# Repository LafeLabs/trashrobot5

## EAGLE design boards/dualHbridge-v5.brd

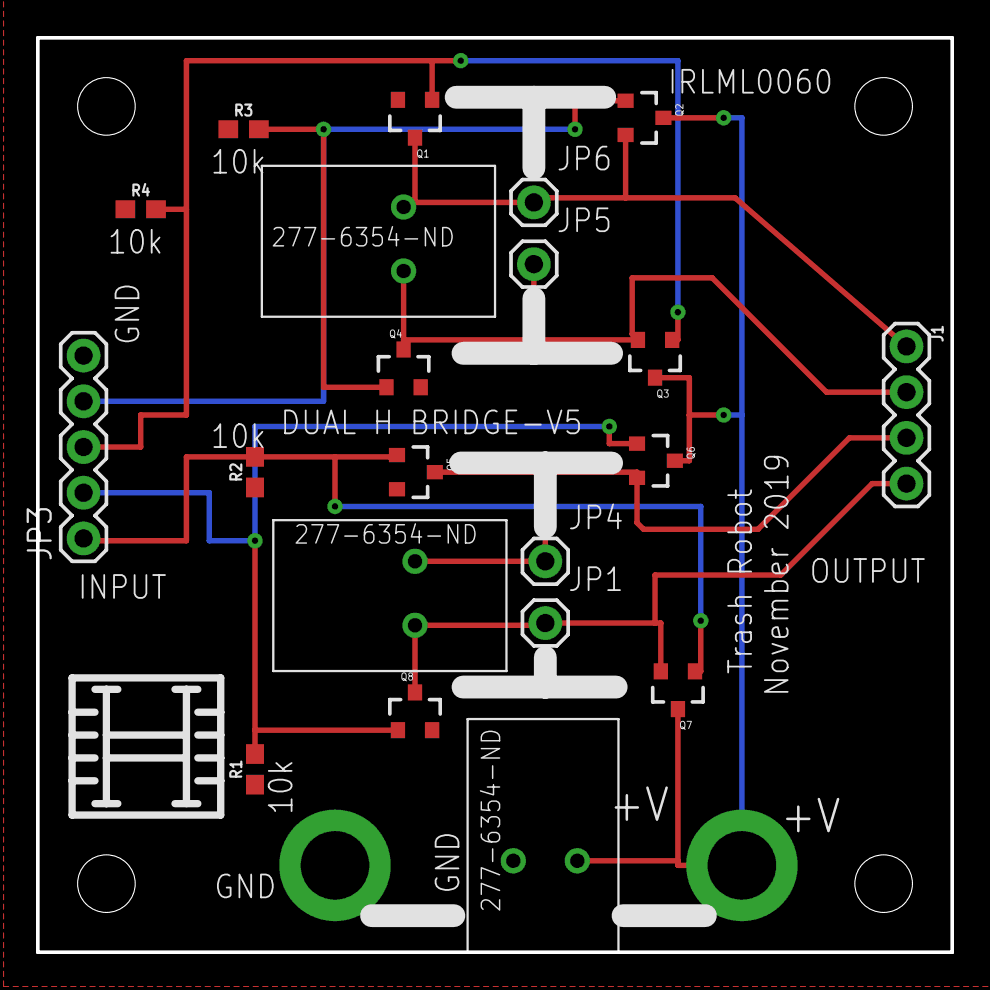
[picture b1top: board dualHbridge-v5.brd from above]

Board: 2 copper layers, 50.8 x 50.8 mm, 23 parts (0 on the bottom side), 10 nets.

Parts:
J1: 1X04
JP1, JP4, JP5, JP6: M01PTH; 1X01@1
JP3: 1X05
JP7, JP8: M01-SMTSO-256-ET; SMTSO-256-ET
Q1, Q2, Q3, Q4, Q5, Q6, Q7, Q8: IRLML0060; SOT-23
R1, R2, R3, R4: 10k; 0603
X1, X2, X3: SPRING-TERMINAL

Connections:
A+: J1.1, JP6.1, Q1.3, Q2.2, X1.P$1
A-: J1.2, JP5.1, Q3.2, Q4.3, X1.P$2
B+: J1.3, JP4.1, Q5.3, Q6.2, X2.P$1
B-: J1.4, JP1.1, Q7.2, Q8.3, X2.P$2
GND: JP3.5, JP8.P$1, Q1.2, Q4.2, Q5.2, Q8.2, R1.1, R2.1, R3.1, R4.1, X3.P$2
unnamed: JP3.4, Q2.1, Q4.1, R3.2
unnamed: JP3.3, Q1.1, Q3.1, R4.2
unnamed: JP3.1, Q5.1, Q7.1, R2.2
unnamed: JP3.2, Q6.1, Q8.1, R1.2
PWR: JP7.P$1, Q2.3, Q3.3, Q6.3, Q7.3, X3.P$1

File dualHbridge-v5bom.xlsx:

REFDES | Value | QTY | Manufacturer | Manufacturer Part Number | Digikey Part Number | package | Price
Q1 | IRLML0060 | 1 | Infineon | IRLML0060 | IRLML0060TRPBFCT-ND |  | 0.25
Q2 | IRLML0060 | 1 | Infineon | IRLML0060 | IRLML0060TRPBFCT-ND |  | 0.25
Q3 | IRLML0060 | 1 | Infineon | IRLML0060 | IRLML0060TRPBFCT-ND |  | 0.25
Q4 | IRLML0060 | 1 | Infineon | IRLML0060 | IRLML0060TRPBFCT-ND |  | 0.25
Q5 | IRLML0060 | 1 | Infineon | IRLML0060 | IRLML0060TRPBFCT-ND |  | 0.25
Q6 | IRLML0060 | 1 | Infineon | IRLML0060 | IRLML0060TRPBFCT-ND |  | 0.25
Q7 | IRLML0060 | 1 | Infineon | IRLML0060 | IRLML0060TRPBFCT-ND |  | 0.25
Q8 | IRLML0060 | 1 | Infineon | IRLML0060 | IRLML0060TRPBFCT-ND |  | 0.25
X1 | spring contact | 3 | Phoenix Contact | 1984963 | 277-6354-ND
X2 |  |  | Phoenix Contact | 1984963 | 277-6354-ND
X3 |  |  | Phoenix Contact | 1984963 | 277-6354-ND
R1 | 10k | 4 | stackpole electronics | ERJ-3EKF3301V | RNCP0603FTD10K0CT-ND | 0603 | 2.7E-2
R2 | 10k |  | stackpole electronics | ERJ-3EKF3301V | RNCP0603FTD10K0CT-ND | 0603 | 2.7E-2
R3 | 10k |  | stackpole electronics | ERJ-3EKF3301V | RNCP0603FTD10K0CT-ND | 0603 | 2.7E-2
R4 | 10k |  | stackpole electronics | ERJ-3EKF3301V | RNCP0603FTD10K0CT-ND | 0603 | 2.7E-2
J1 | 4 pin header | 1 | Samtec | TSW-104-25-G-S-RA |  |  | 0.25
J1 | 5 pin header | 1 | Samtec | TSW-105-25-G-S-RA |  |  | 0.25
total |  |  |  |  |  |  | 2

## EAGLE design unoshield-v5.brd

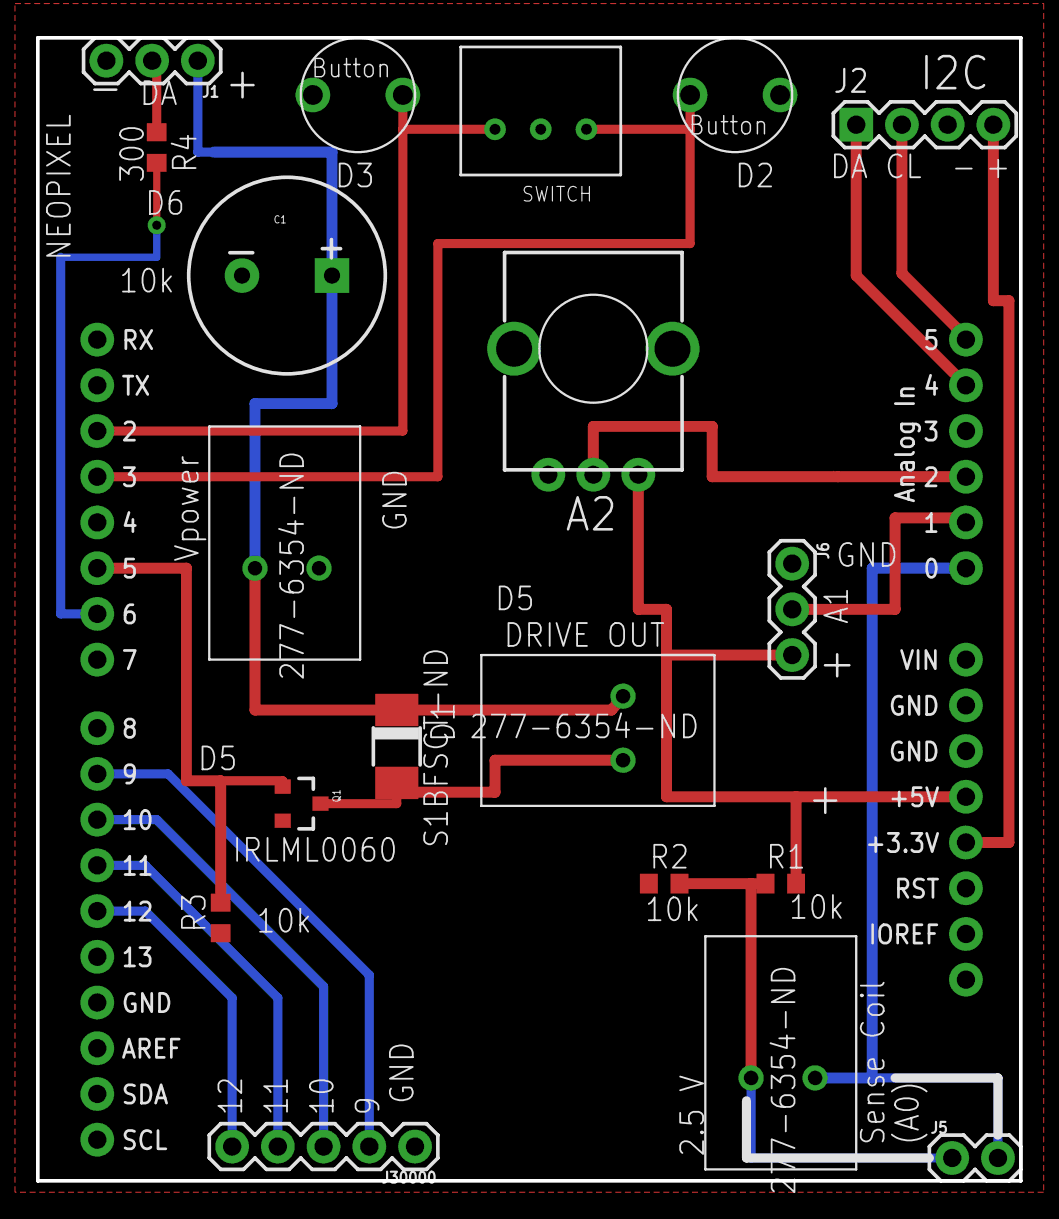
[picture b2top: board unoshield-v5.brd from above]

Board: 2 copper layers, 54.6 x 63.5 mm, 20 parts (0 on the bottom side), 20 nets.

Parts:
C1: 1000uf/25V; CPOL-RADIAL-1000UF-25V-KIT
D1: DO-214AC
J1, J6: 455-1750-1-ND; 1X03
J2: 1X04
J4: ARDUINO_R3_SHIELD; UNO_R3_SHIELD
J5: 1X02
J30000: 1X05
Q1: IRLML0060; SOT-23
R1, R2, R3: 10k; R0603
R4: 330; R0603
R5: 20k; ALPS_POT_KIT
SW1, SW2: BUTTON
SW3: ON-OFF-ON-360-1013-ND; 360-1013-ND
X1, X2, X3: SPRING-TERMINAL

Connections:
5V: J4.5V, J6.3, R1.2, R5.P$3
BUTTON: J4.D3, SW2.P$1, SW3.RIGHT
CL: J2.2, J4.A5
DA: J2.1, J4.A4
GND: C1.-, J1.3, J2.3, J4.GND@0, J4.GND@1, J4.GND@2, J6.1, J30000.1, Q1.2, R2.1, R3.1, R5.P$1, SW1.P$2, SW2.P$2, SW3.CENTER, X1.P$1
unnamed: J4.D5, Q1.1, R3.2
unnamed: J4.D6, R4.2
unnamed: J5.1, R1.1, R2.2, X2.P$2
unnamed: J4.A1, J6.2
unnamed: J4.D12, J30000.5
unnamed: D1.A, Q1.3, X3.P$2
unnamed: J4.D11, J30000.4
unnamed: J4.D10, J30000.3
unnamed: J4.D9, J30000.2
unnamed: J4.D2, SW1.P$1, SW3.LEFT
unnamed: J4.A0, J5.2, X2.P$1
unnamed: J1.2, R4.1
unnamed: J4.A2, R5.P$2
VCC: J2.4, J4.3.3V
VIN: C1.+, D1.C, J1.1, X1.P$2, X3.P$1

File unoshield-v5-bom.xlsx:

REFDES | Value | QTY | Manufacturer | Manufacturer Part Number | Digikey Part Number | package | Price
Q1 | IRLML0060 | 1 | Infineon | IRLML0060 | IRLML0060TRPBFCT-ND |  | 0.25
D1 |  | 1 | ON semiconductor | S1B | S1BFSCT-ND | DO-214AC | 0.2
X1 | spring contact | 3 | Phoenix Contact | 1984963 | 277-6354-ND |  | 0.3
X2 |  |  | Phoenix Contact | 1984963 | 277-6354-ND |  | 0.3
X3 |  |  | Phoenix Contact | 1984963 | 277-6354-ND |  | 0.3
R1 | 10k | 3 | stackpole electronics | ERJ-3EKF3301V | RNCP0603FTD10K0CT-ND | 0603 | 2.7E-2
R2 | 10k |  | stackpole electronics | ERJ-3EKF3301V | RNCP0603FTD10K0CT-ND | 0603 | 2.7E-2
R3 | 10k |  | stackpole electronics | ERJ-3EKF3301V | RNCP0603FTD10K0CT-ND | 0603 | 2.7E-2
R4 | 300 | 1 | susumu | RR0816P-301-D | RR08P300DCT-ND | 0603 | 3.6999999999999998E-2
R5 | 20k pot | 1 | Bourns, inc | PTV09A-4030U-B203 | PTV09A-4030U-B203-ND |  | 0.75
R5b | 10k pot | 1 | Bourns, inc | PTV09A-4225F-B103 | PTV09A-4225F-B103-ND |  | 0.75
C1 | 1000uF | 1 | Rubycon | 35PX1000MEFC10X20 | 1189-1745-ND | can | 0.51
SW1 | button | 2 | panasonic | EVQ-11D05B | P15931SCT-ND |  | 0.22600000000000001
SW2 | button |  | panasonic | EVQ-11D05B | P15931SCT-ND |  | 0.23
SW3 | switches | 1 | NKK switches | B13AP | 360-1013-ND |  | 3.54
J1 | 5 pin RA | 1 | samtec | TSW-105-25-G-S-RA | TSW-105-25-G-S-RA-ND |  | 0.68
j2 | -
j3 | -
J4 | arduino header set | 1 | adafruit | 85 | 1528-1074-ND |  | 1.95
total |  |  |  |  |  |  | 10.103999999999999
cart: https://www.digikey.com/short/pdm7tc

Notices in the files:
parts and their libraries:
SparkFun-Connectors: Licensing: Creative Commons ShareAlike 4.0 International - https://creativecommons.org/licenses/by-sa/4.0
